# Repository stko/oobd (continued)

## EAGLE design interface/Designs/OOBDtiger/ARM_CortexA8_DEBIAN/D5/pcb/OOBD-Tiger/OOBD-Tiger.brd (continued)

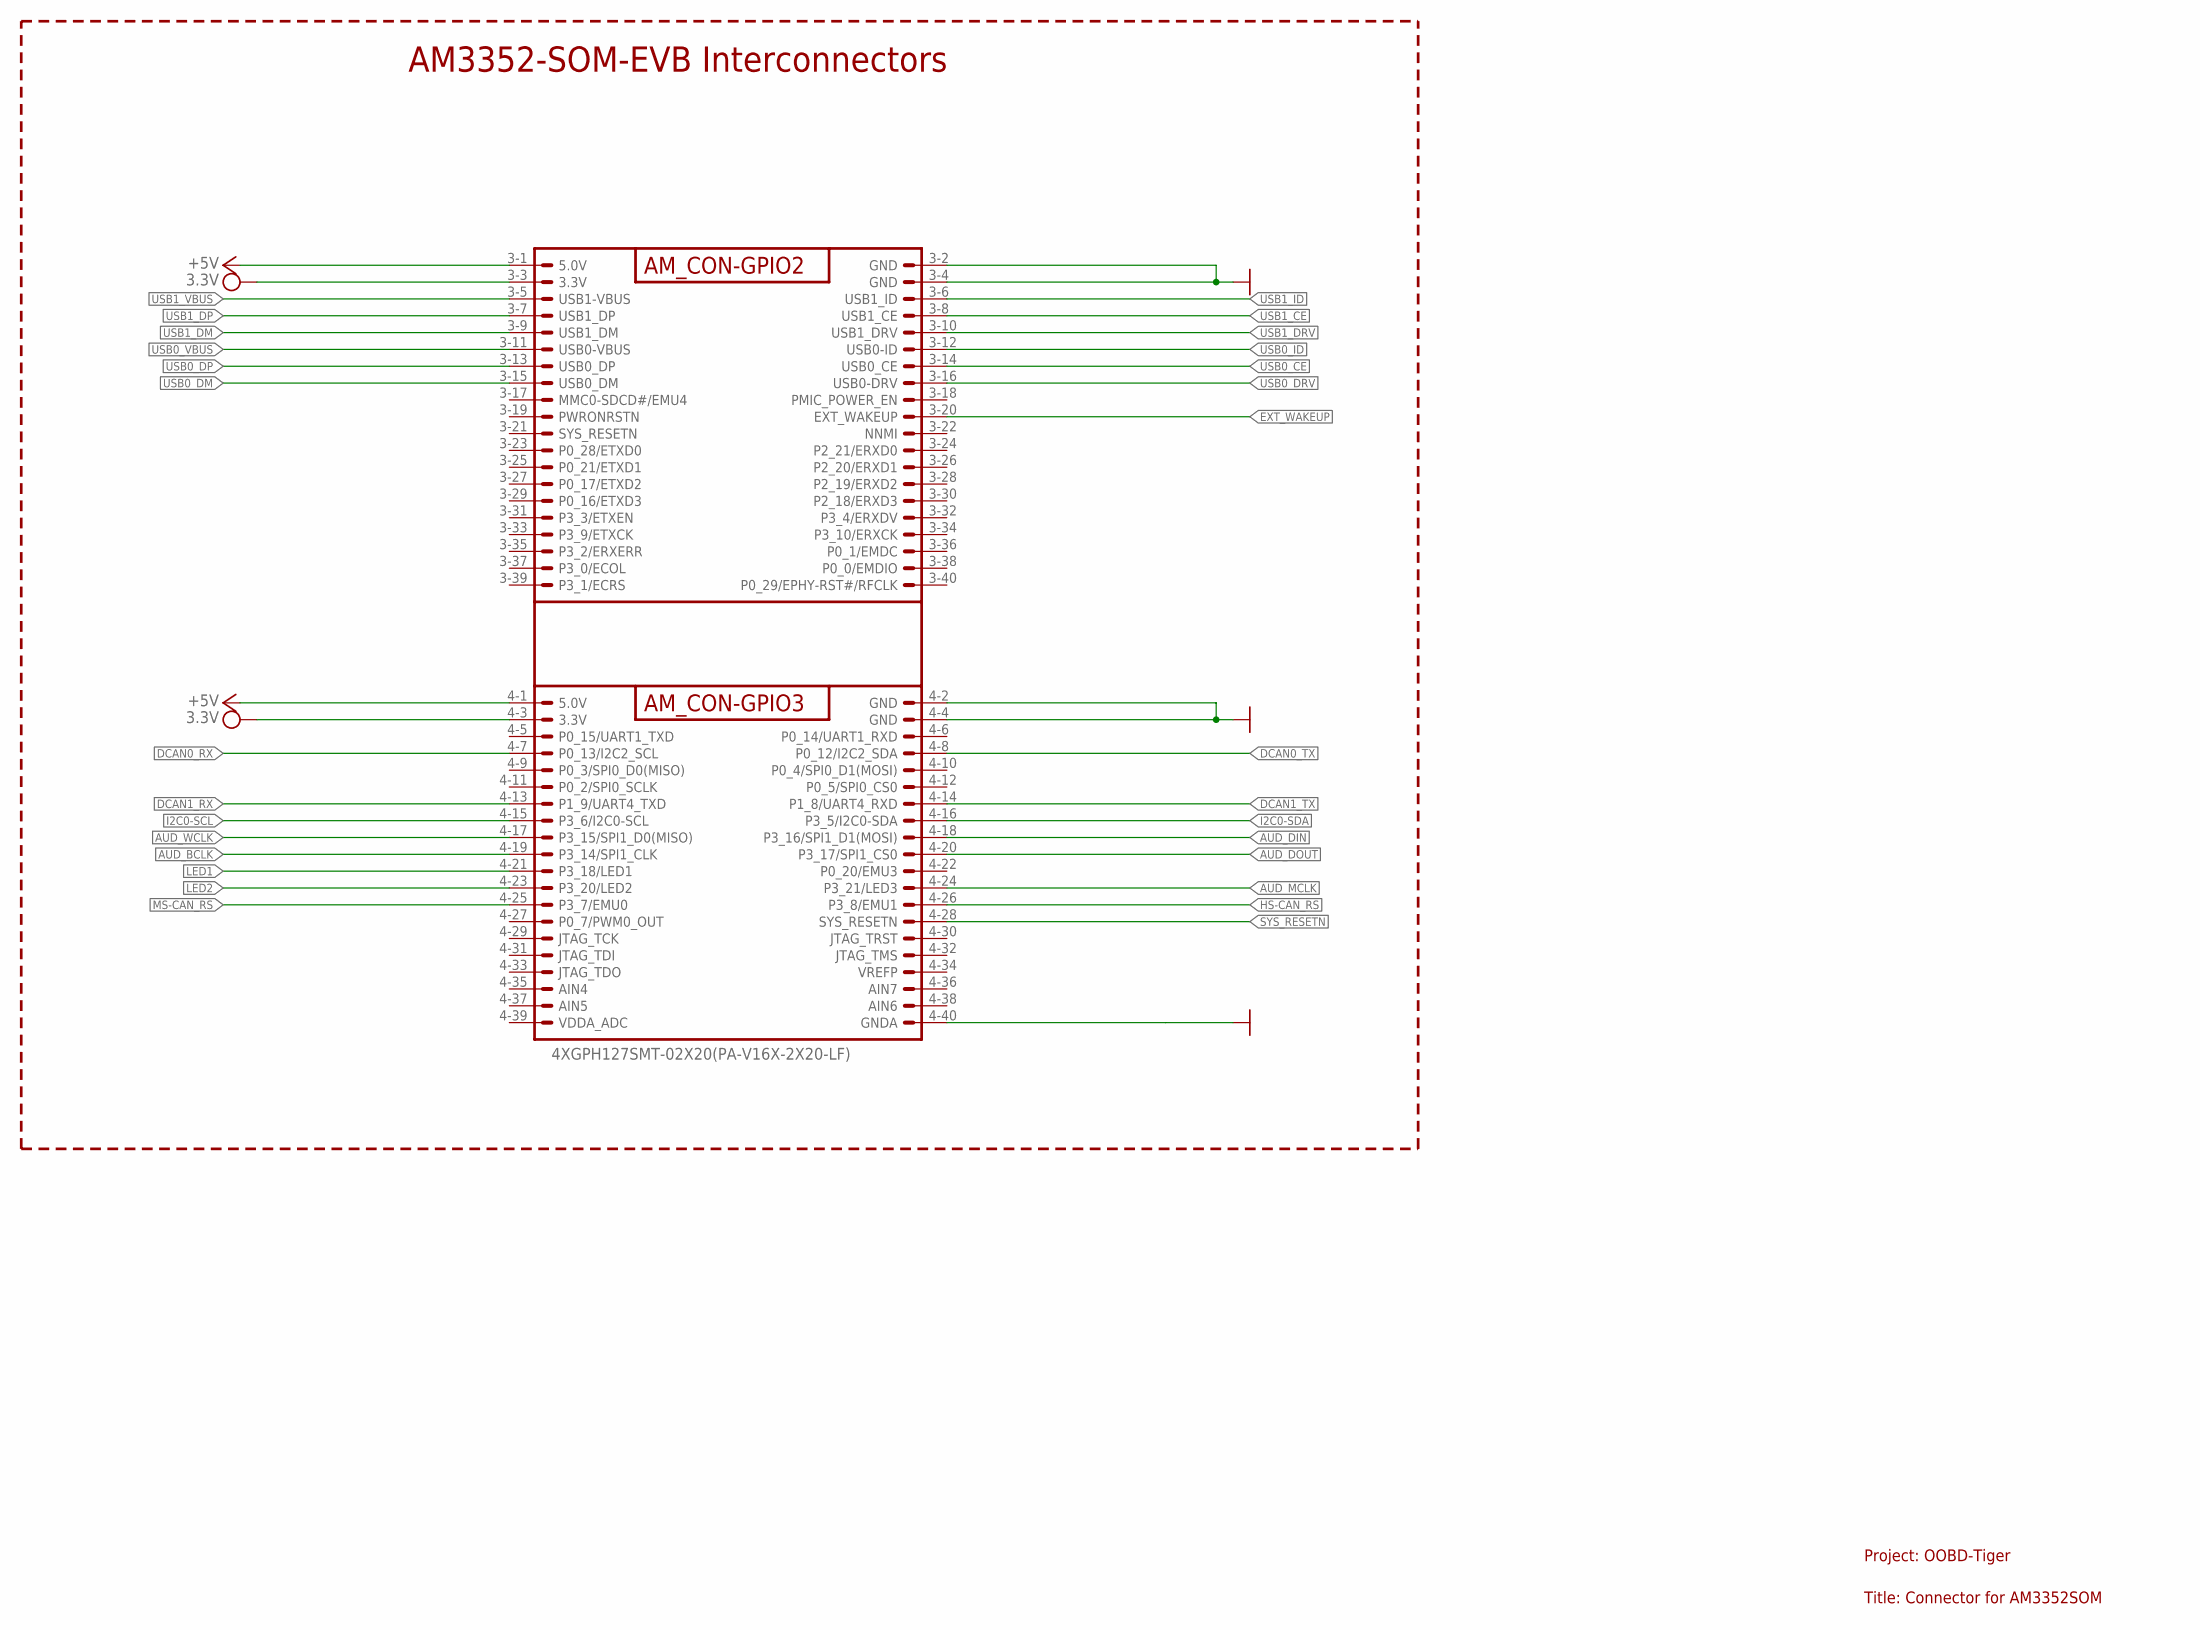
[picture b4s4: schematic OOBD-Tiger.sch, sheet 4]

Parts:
AM3352-SOM-EVB-PLATFORM: 4XGPH127SMT-02X20(PA-V16X-2X20-LF); OOBD-TIGER-AM3352-SOM

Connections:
3V3: AM3352-SOM-EVB-PLATFORM.3-3 (3.3V), AM3352-SOM-EVB-PLATFORM.4-3 (3.3V)
+5V: AM3352-SOM-EVB-PLATFORM.3-1 (5.0V), AM3352-SOM-EVB-PLATFORM.4-1 (5.0V); also elsewhere on the board
AUD_BCLK: AM3352-SOM-EVB-PLATFORM.4-19 (P3_14/SPI1_CLK); also elsewhere on the board
AUD_DIN: AM3352-SOM-EVB-PLATFORM.4-18 (P3_16/SPI1_D1(MOSI)); also elsewhere on the board
AUD_DOUT: AM3352-SOM-EVB-PLATFORM.4-20 (P3_17/SPI1_CS0); also elsewhere on the board
AUD_MCLK: AM3352-SOM-EVB-PLATFORM.4-24 (P3_21/LED3); also elsewhere on the board
AUD_WCLK: AM3352-SOM-EVB-PLATFORM.4-17 (P3_15/SPI1_D0(MISO)); also elsewhere on the board
DCAN0_RX: AM3352-SOM-EVB-PLATFORM.4-7 (P0_13/I2C2_SCL); also elsewhere on the board
DCAN0_TX: AM3352-SOM-EVB-PLATFORM.4-8 (P0_12/I2C2_SDA); also elsewhere on the board
DCAN1_RX: AM3352-SOM-EVB-PLATFORM.4-13 (P1_9/UART4_TXD); also elsewhere on the board
DCAN1_TX: AM3352-SOM-EVB-PLATFORM.4-14 (P1_8/UART4_RXD); also elsewhere on the board
EXT_WAKEUP: AM3352-SOM-EVB-PLATFORM.3-20 (EXT_WAKEUP); also elsewhere on the board
GND: AM3352-SOM-EVB-PLATFORM.3-2 (GND), AM3352-SOM-EVB-PLATFORM.3-4 (GND), AM3352-SOM-EVB-PLATFORM.4-2 (GND), AM3352-SOM-EVB-PLATFORM.4-4 (GND), AM3352-SOM-EVB-PLATFORM.4-40 (GNDA); also elsewhere on the board
HS-CAN_RS: AM3352-SOM-EVB-PLATFORM.4-26 (P3_8/EMU1); also elsewhere on the board
I2C0-SCL: AM3352-SOM-EVB-PLATFORM.4-15 (P3_6/I2C0-SCL); also elsewhere on the board
I2C0-SDA: AM3352-SOM-EVB-PLATFORM.4-16 (P3_5/I2C0-SDA); also elsewhere on the board
LED1: AM3352-SOM-EVB-PLATFORM.4-21 (P3_18/LED1); also elsewhere on the board
LED2: AM3352-SOM-EVB-PLATFORM.4-23 (P3_20/LED2); also elsewhere on the board
MS-CAN_RS: AM3352-SOM-EVB-PLATFORM.4-25 (P3_7/EMU0); also elsewhere on the board
SYS_RESETN: AM3352-SOM-EVB-PLATFORM.4-28 (SYS_RESETN); also elsewhere on the board
USB0_CE: AM3352-SOM-EVB-PLATFORM.3-14 (USB0_CE); also elsewhere on the board
USB0_DM: AM3352-SOM-EVB-PLATFORM.3-15 (USB0_DM); also elsewhere on the board
USB0_DP: AM3352-SOM-EVB-PLATFORM.3-13 (USB0_DP); also elsewhere on the board
USB0_DRV: AM3352-SOM-EVB-PLATFORM.3-16 (USB0-DRV); also elsewhere on the board
USB0_ID: AM3352-SOM-EVB-PLATFORM.3-12 (USB0-ID); also elsewhere on the board
USB0_VBUS: AM3352-SOM-EVB-PLATFORM.3-11 (USB0-VBUS); also elsewhere on the board
USB1_CE: AM3352-SOM-EVB-PLATFORM.3-8 (USB1_CE); also elsewhere on the board
USB1_DM: AM3352-SOM-EVB-PLATFORM.3-9 (USB1_DM); also elsewhere on the board
USB1_DP: AM3352-SOM-EVB-PLATFORM.3-7 (USB1_DP); also elsewhere on the board
USB1_DRV: AM3352-SOM-EVB-PLATFORM.3-10 (USB1_DRV); also elsewhere on the board
USB1_ID: AM3352-SOM-EVB-PLATFORM.3-6 (USB1_ID); also elsewhere on the board
USB1_VBUS: AM3352-SOM-EVB-PLATFORM.3-5 (USB1-VBUS); also elsewhere on the board

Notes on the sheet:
AM3352-SOM-EVB Interconnectors
Project: OOBD-Tiger
Title: Connector for AM3352SOM

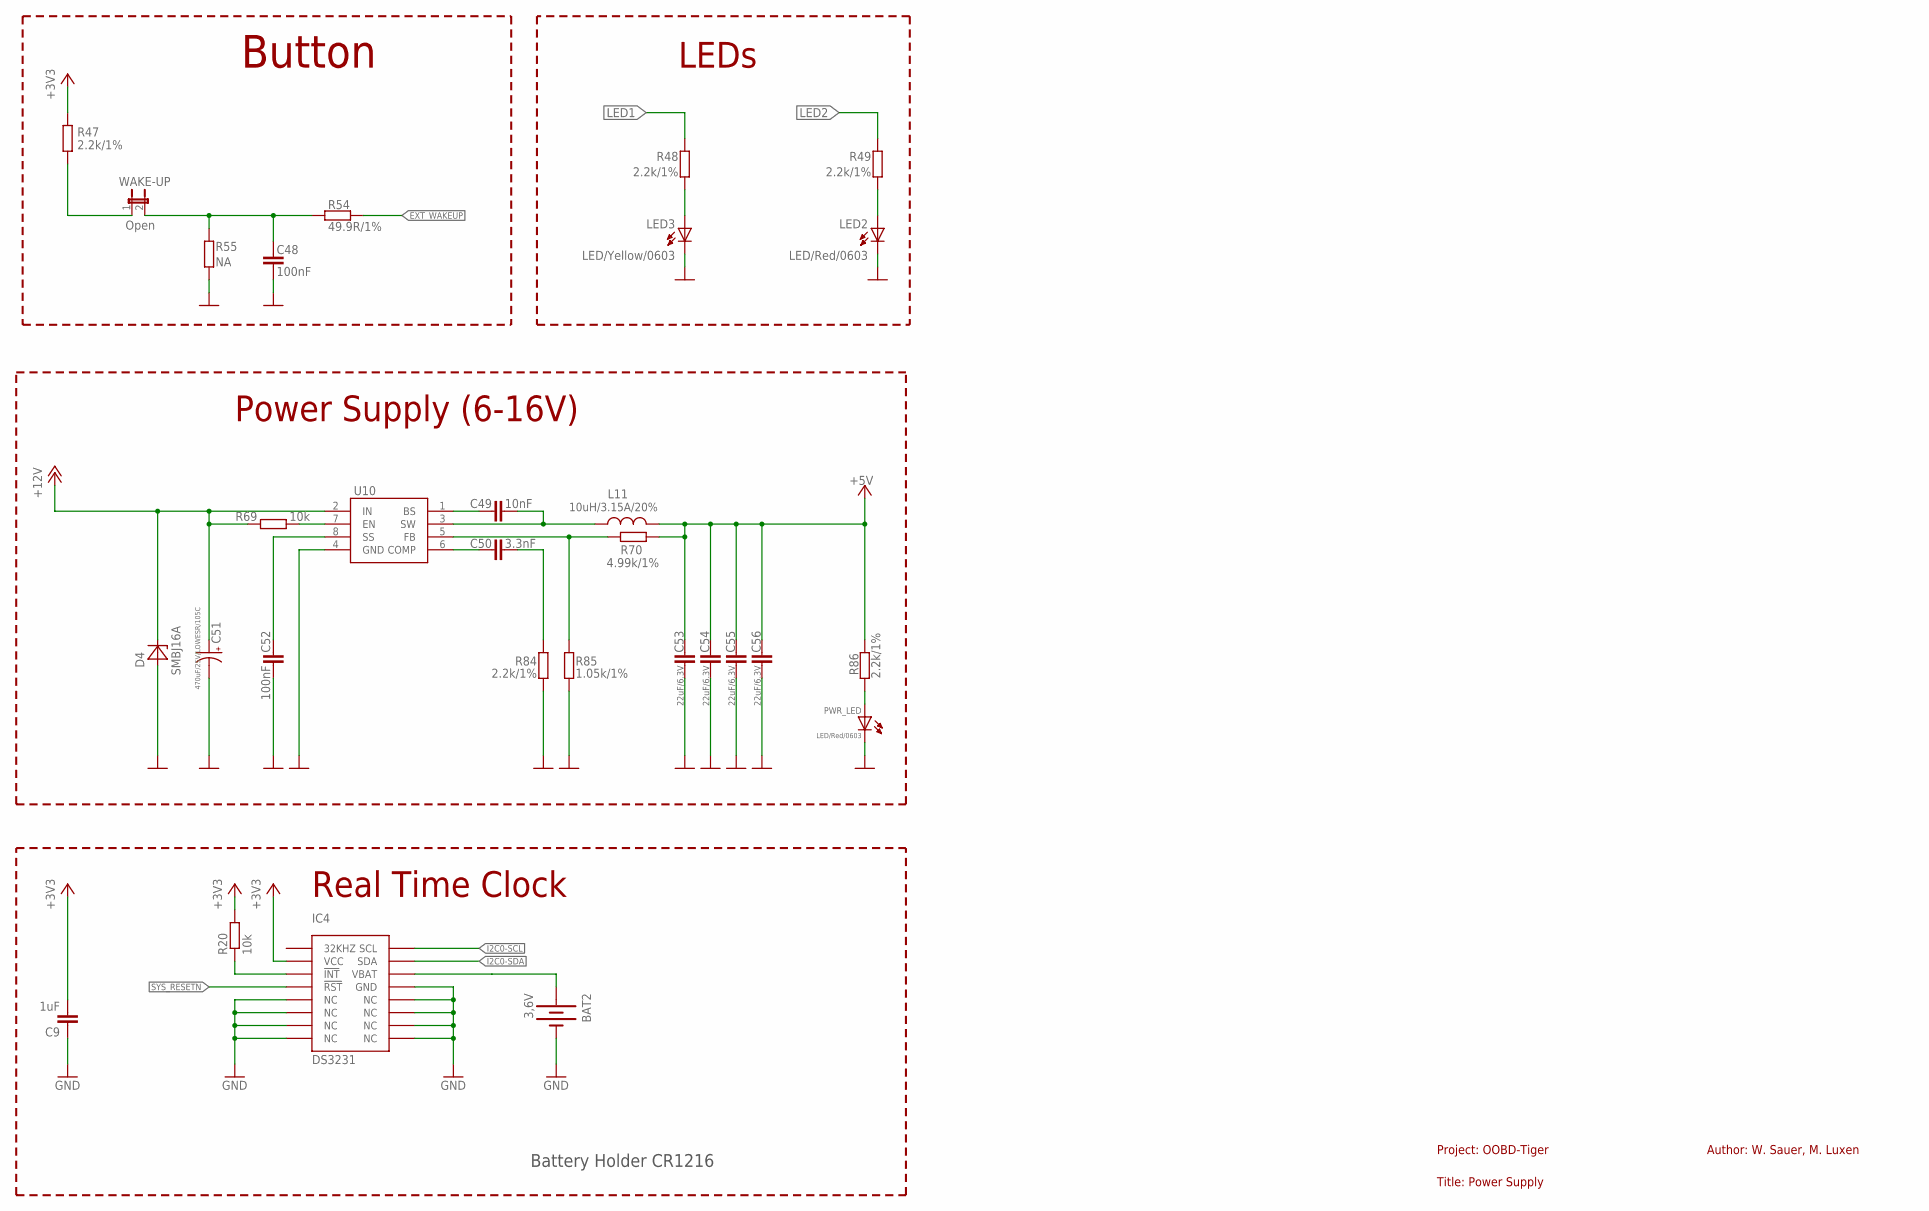
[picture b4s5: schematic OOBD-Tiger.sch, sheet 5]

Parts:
BAT2: 3,6V; BATTCON_12MM_PTH
C9: 1uF; C0603
C48, C52: 100nF; C0603
C49: 10nF; C0603
C50: 3.3nF; C0603
C51: 470uF/25V/LOWESR/105C; PANASONIC_D
C53, C54, C55, C56: 22uF/6.3V; C0603
D4: SMBJ16A; DO214AA
IC4: DS3231; SOIC-16W
L11: 10uH/3.15A/20%; 8X8MM_3131
LED2: LED/Red/0603; LED_0603
LED3: LED/Yellow/0603; LED_0603
PWR_LED: LED/Red/0603; LED-0603
R20, R69: 10k; R0603
R47, R48, R49, R84, R86: 2.2k/1%; R0603
R54: 49.9R/1%; R0603
R55: NA; R0603
R70: 4.99k/1%; R0603
R85: 1.05k/1%; R0603
U10: MP1482DS; SOIC8
WAKE-UP: Open; 1X02_LOCK

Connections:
+3V3: C9.2, IC4.2 (VCC), R20.2, R47.2; also elsewhere on the board
+5V: C53.1, C54.1, C55.1, C56.1, L11.2, R70.2, R86.1; also elsewhere on the board
+12V: C51.+, D4.C, R69.1, U10.2 (IN); also elsewhere on the board
EXT_WAKEUP: R54.1; also elsewhere on the board
GND: BAT2.GND (-), C9.1, C48.2, C51.-, C52.2, C53.2, C54.2, C55.2, C56.2, D4.A, IC4.5 (NC), IC4.6 (NC), IC4.7 (NC), IC4.8 (NC), IC4.9 (NC), IC4.10 (NC), IC4.11 (NC), IC4.12 (NC), IC4.13 (GND), LED2.C, LED3.C, PWR_LED.C, R55.2, R84.2, R85.2, U10.4 (GND); also elsewhere on the board
I2C0-SCL: IC4.16 (SCL); also elsewhere on the board
I2C0-SDA: IC4.15 (SDA); also elsewhere on the board
LED1: R48.1; also elsewhere on the board
LED2: R49.1; also elsewhere on the board
unnamed: LED2.A, R49.2
unnamed: C52.1, U10.8 (SS)
unnamed: R69.2, U10.7 (EN)
unnamed: C49.1, U10.1 (BS)
unnamed: C49.2, L11.1, U10.3 (SW)
unnamed: C50.1, U10.6 (COMP)
unnamed: C50.2, R84.1
unnamed: IC4.3 (!INT), R20.1
unnamed: R47.1, WAKE-UP.1
unnamed: C48.1, R54.2, R55.1, WAKE-UP.2
unnamed: R70.1, R85.1, U10.5 (FB)
unnamed: PWR_LED.A, R86.2
unnamed: LED3.A, R48.2
SYS_RESETN: IC4.4 (!RST); also elsewhere on the board
VBAT: BAT2.VCC@1 (+), IC4.14 (VBAT)

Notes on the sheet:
Button
LEDs
Power Supply (6-16V)
Author: W. Sauer, M. Luxen
Project: OOBD-Tiger
Title: Power Supply
Real Time Clock
Battery Holder CR1216

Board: 2 copper layers, 136 parts (57 on the bottom side), 91 nets, no tracks yet.

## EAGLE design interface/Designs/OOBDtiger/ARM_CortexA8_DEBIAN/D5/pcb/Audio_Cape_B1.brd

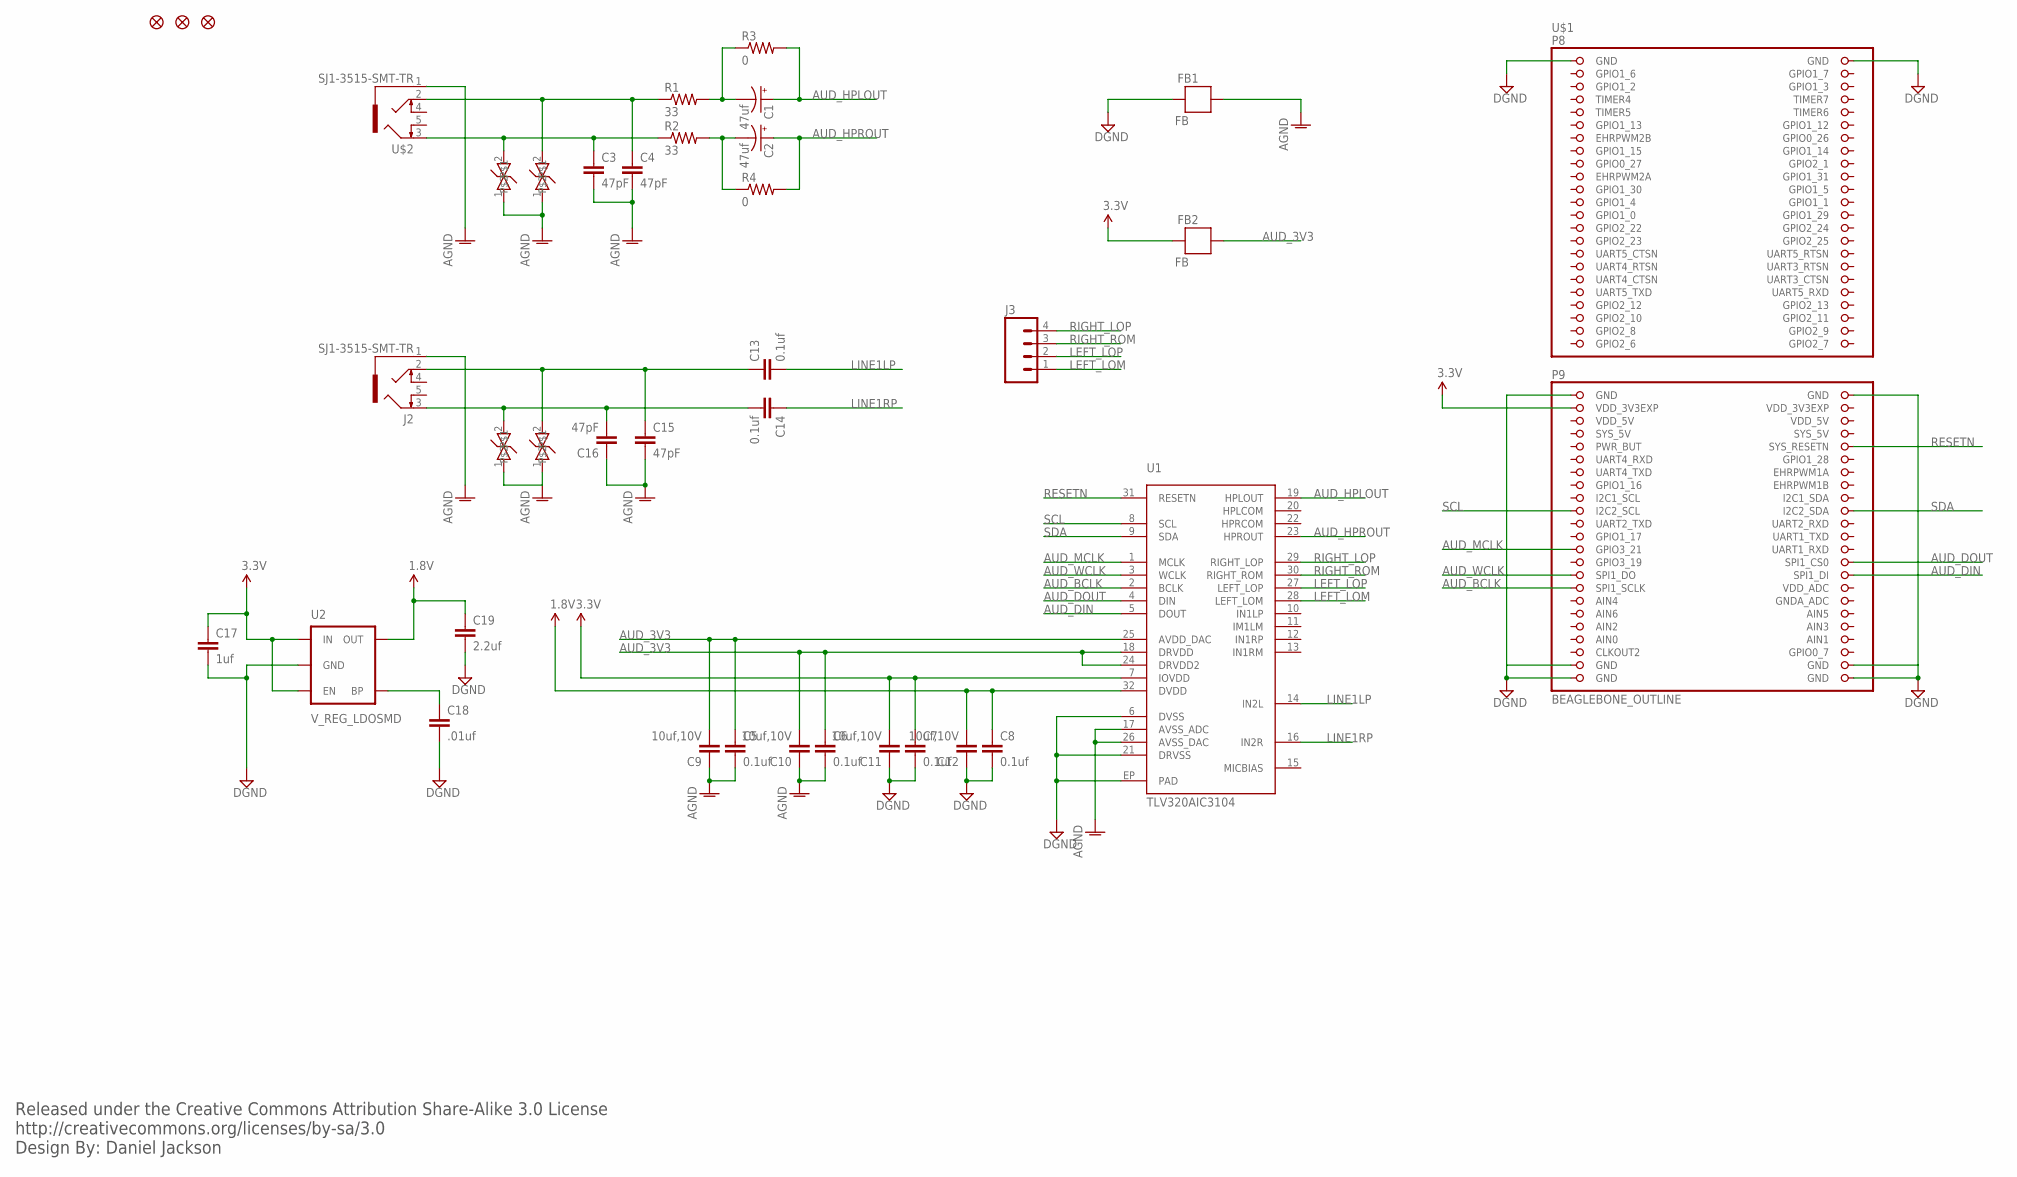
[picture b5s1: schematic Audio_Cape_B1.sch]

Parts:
C1, C2: 47uf; EIA3216
C3, C4, C15, C16: 47pF; 0402-CAP
C5, C6, C7, C8, C13, C14: 0.1uf; 0402-CAP
C9, C10, C11, C12: 10uf,10V; 0603-CAP
C17: 1uf; 0402-CAP
C18: .01uf; 0402-CAP
C19: 2.2uf; 0402-CAP
D1, D2, D3, D4: PGB0010603MR; 0603
FB1, FB2: FB; 0603
FID1, FID2, FID3: FIDUCIAL1X2.5; FIDUCIAL-1X2.5
J2: SJ1-3515-SMT-TR; JACK-SMT
J3: M04PTH; 1X04
R1, R2: 33; 0402-RES
R3, R4: 0; 0805
U1: TLV320AIC3104; QFN-32
U2: V_REG_LDOSMD; SOT23-5
U$1: BEAGLEBONE_OUTLINE; BEAGLEBONE_SHIELD
U$2: SJ1-3515-SMT-TR; JACK-SMT

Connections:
1.8V: C8.1, C12.2, C19.1, U1.32 (DVDD), U2.5 (OUT)
3.3V: C7.1, C11.2, C17.1, FB2.2, U1.7 (IOVDD), U2.1 (IN), U2.3 (EN), U$1.49 (VDD_3V3EXP)
AGND: C3.2, C4.2, C5.2, C6.2, C9.1, C10.1, C15.2, C16.1, D1.1, D2.1, D3.1, D4.1, FB1.1, J2.1, U1.17 (AVSS_ADC), U1.26 (AVSS_DAC), U$2.1
AIN0: U$1.85 (AIN0)
AUD_3V3: C5.1, C6.1, C9.2, C10.2, FB2.1, U1.18 (DRVDD), U1.24 (DRVDD2), U1.25 (AVDD_DAC)
AUD_BCLK: U1.2 (BCLK), U$1.77 (SPI1_SCLK)
AUD_DIN: U1.5 (DOUT), U$1.76 (SPI1_DI)
AUD_DOUT: U1.4 (DIN), U$1.74 (SPI1_CS0)
AUD_HPLOUT: C1.A (+), R3.2, U1.19 (HPLOUT)
AUD_HPROUT: C2.A (+), R4.2, U1.23 (HPROUT)
AUD_MCLK: U1.1 (MCLK), U$1.71 (GPIO3_21)
AUD_WCLK: U1.3 (WCLK), U$1.75 (SPI1_DO)
DGND: C7.2, C8.2, C11.1, C12.1, C17.2, C18.2, C19.2, FB1.2, U1.6 (DVSS), U1.21 (DRVSS), U1.EP (PAD), U2.2 (GND), U$1.1 (GND), U$1.2 (GND), U$1.47 (GND), U$1.48 (GND), U$1.89 (GND), U$1.90 (GND), U$1.91 (GND), U$1.92 (GND)
J1: C4.1, D2.2, R1.1, U$2.2
LEFT_LOM: J3.1, U1.28 (LEFT_LOM)
LEFT_LOP: J3.2, U1.27 (LEFT_LOP)
LINE1LP: C13.2, U1.14 (IN2L)
LINE1RP: C14.1, U1.16 (IN2R)
unnamed: C14.2, C16.2, D3.2, J2.3
unnamed: C1.C (-), R1.2, R3.1
unnamed: C2.C (-), R2.2, R4.1
unnamed: C3.1, D1.2, R2.1, U$2.3
unnamed: C13.1, C15.1, D4.2, J2.2
unnamed: C18.1, U2.4 (BP)
RESETN: U1.31 (RESETN), U$1.56 (SYS_RESETN)
RIGHT_LOP: J3.4, U1.29 (RIGHT_LOP)
RIGHT_ROM: J3.3, U1.30 (RIGHT_ROM)
SCL: U1.8 (SCL), U$1.65 (I2C2_SCL)
SDA: U1.9 (SDA), U$1.66 (I2C2_SDA)
SYS_5V: U$1.53 (SYS_5V)
VDD_3V3EXP: U$1.50 (VDD_3V3EXP)
VDD_5V: U$1.51 (VDD_5V), U$1.52 (VDD_5V)

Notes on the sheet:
Released under the Creative Commons Attribution Share-Alike 3.0 License http://creativecommons.org/licenses/by-sa/3.0 Design By: Daniel Jackson

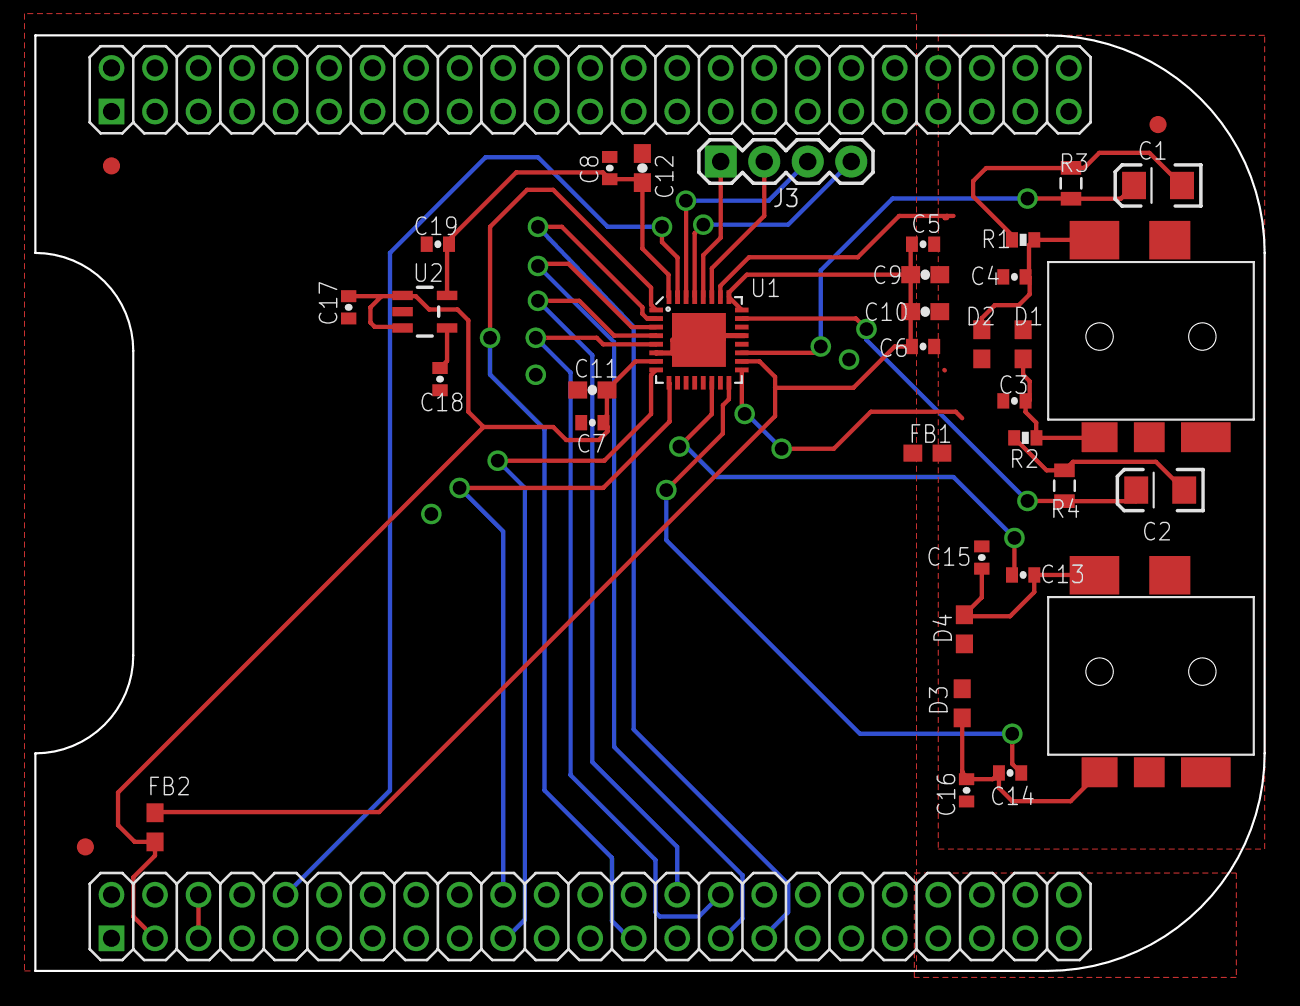
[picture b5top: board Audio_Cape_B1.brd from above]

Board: 2 copper layers, 71.8 x 54.6 mm, 40 parts (0 on the bottom side), 29 nets.

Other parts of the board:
DRILEGEND: DRILEGEND
U$4: CIRCUITCO-LOGO

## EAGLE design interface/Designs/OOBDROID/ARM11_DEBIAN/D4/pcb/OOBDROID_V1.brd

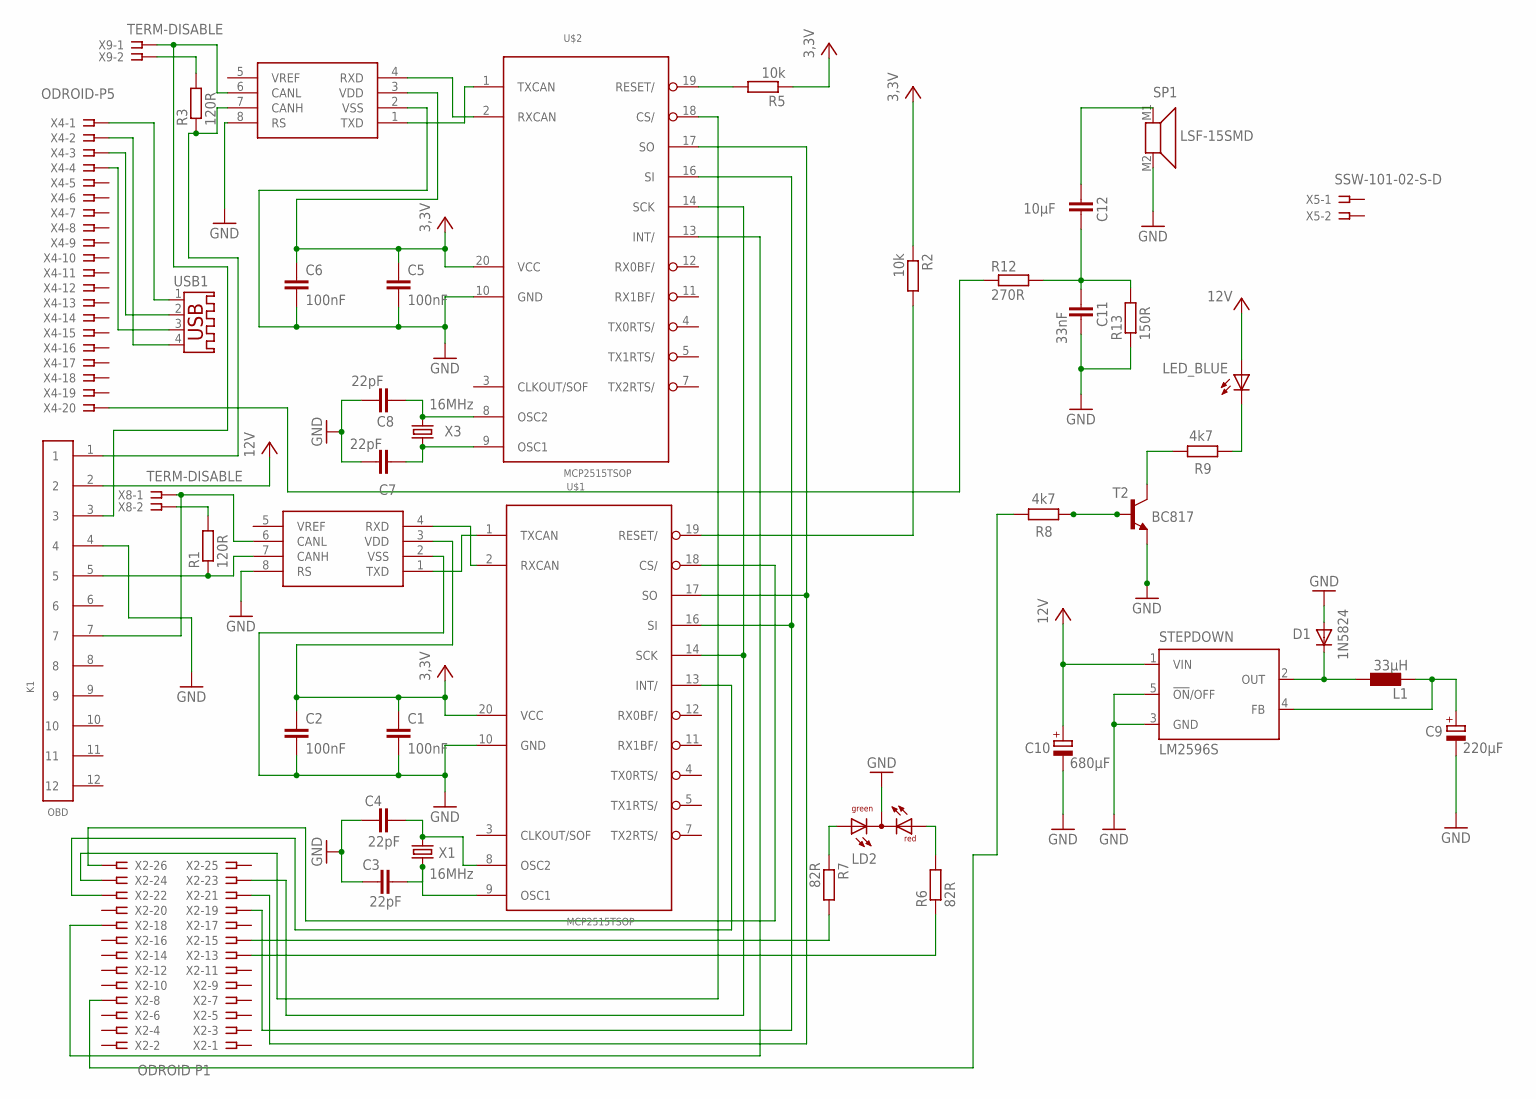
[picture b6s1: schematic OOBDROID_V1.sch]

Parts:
C1, C2, C5, C6: 100nF; C0805
C3, C4, C7, C8: 22pF; C0805
C9: 220µF; E1,8-4
C10: 680µF; E1,8-4
C11: 33nF; C0805
C12: 10µF; C0805
D1: 1N5824; DO214AA
K1: OBD; 653112124022
L1: 33µH; L4532P
LD2: DUOLED-RG-C; DUOLED-C-5MM
LED_BLUE: LED5MM
R1, R3: 120R; R0603
R2, R5: 10k; R0603
R6, R7: 82R; R0603
R8, R9: 4k7; R0603
R12: 270R; R0603
R13: 150R; R0603
SP1: LSF-15SMD; SMS-1308MS-2-R
STEPDOWN: LM2596S; TO263-5
T2: BC817; SOT23
U1, U2: MCP2551; SO08
U$1, U$2: MCP2515TSOP; TSSOP20
USB1: USB-A003
X1, X3: 16MHz; HC49
X2: ODROID P1; SSW-113-02-S-D
X4: ODROID-P5; SSW-120-02-S-S
X5: SSW-101-02-S-D
X8: TERM-DISABLE; SSW-101-02-S-D; MPN CAN-DISABLE
X9: TERM-DISABLE; SSW-101-02-S-D

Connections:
GND: C1.2, C2.2, C3.1, C4.1, C5.2, C6.2, C7.1, C8.1, C9.-, C10.-, C11.1, D1.A, K1.4, LD2.C, R13.1, SP1.M2 (2), STEPDOWN.3 (GND), STEPDOWN.5 (!ON!/OFF), T2.2 (E), U1.2 (VSS), U1.8 (RS), U2.2 (VSS), U2.8 (RS), U$1.10 (GND), U$2.10 (GND)
unnamed: K1.5, R1.1, U1.7 (CANH)
unnamed: D1.C, L1.1, STEPDOWN.2 (OUT)
unnamed: C8.2, U$2.8 (OSC2), X3.2
unnamed: C9.+, L1.2, STEPDOWN.4 (FB)
unnamed: C7.2, U$2.9 (OSC1), X3.1
unnamed: R5.2, U$2.19 (RESET/)
unnamed: U2.4 (RXD), U$2.2 (RXCAN)
unnamed: U2.1 (TXD), U$2.1 (TXCAN)
unnamed: K1.3, U2.6 (CANL), X9.1
unnamed: K1.1, R3.1, U2.7 (CANH)
unnamed: C4.2, U$1.8 (OSC2), X1.2
unnamed: C3.2, U$1.9 (OSC1), X1.1
unnamed: R2.2, U$1.19 (RESET/)
unnamed: U1.4 (RXD), U$1.2 (RXCAN)
unnamed: U1.1 (TXD), U$1.1 (TXCAN)
unnamed: K1.7, U1.6 (CANL), X8.1
unnamed: C12.2, SP1.M1 (1)
unnamed: LED_BLUE.K (C), R9.1
unnamed: U$1.18 (CS/), X2.26
unnamed: R3.2, X9.2
unnamed: LD2.AR, R6.2
unnamed: LD2.AX (AG), R7.1
unnamed: R7.2, X2.15
unnamed: R6.1, X2.13
unnamed: USB1.1, X4.1
unnamed: USB1.4, X4.2
unnamed: USB1.2, X4.3
unnamed: USB1.3, X4.4
unnamed: R12.1, X4.20
unnamed: U$1.13 (INT/), X2.22
unnamed: U$2.13 (INT/), X2.18
unnamed: U$2.18 (CS/), X2.24
unnamed: R9.2, T2.3 (C)
unnamed: R8.1, T2.1 (B)
unnamed: R8.2, X2.8
unnamed: C11.2, C12.1, R12.2, R13.2
unnamed: U$1.16 (SI), U$2.16 (SI), X2.19
unnamed: R1.2, X8.2
unnamed: U$1.17 (SO), U$2.17 (SO), X2.21
unnamed: U$1.14 (SCK), U$2.14 (SCK), X2.23
VCC: C1.1, C2.1, C5.1, C6.1, C10.+, K1.2, LED_BLUE.A, R2.1, R5.1, STEPDOWN.1 (VIN), U1.3 (VDD), U2.3 (VDD), U$1.20 (VCC), U$2.20 (VCC)

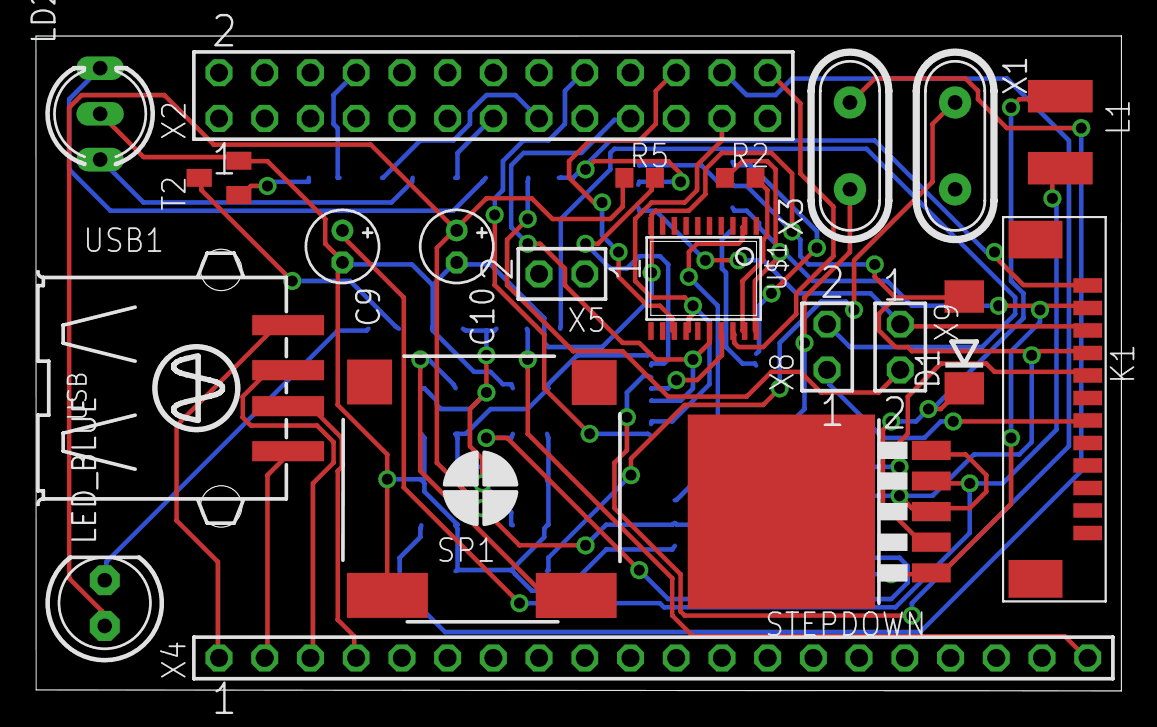
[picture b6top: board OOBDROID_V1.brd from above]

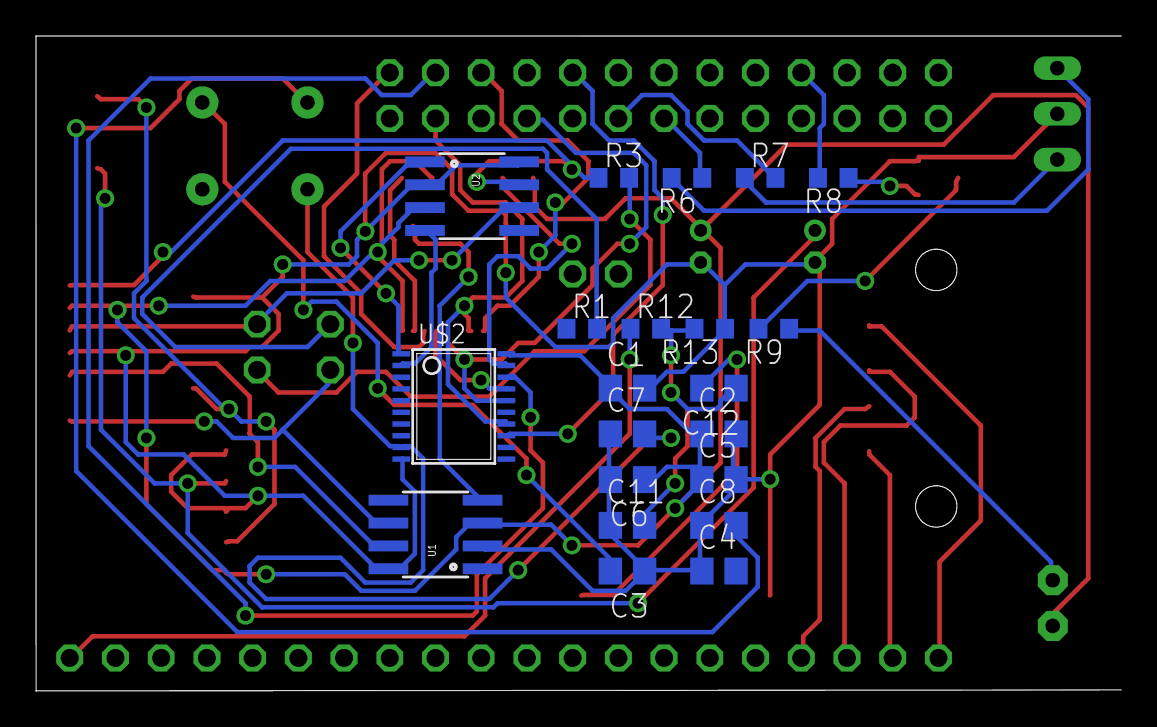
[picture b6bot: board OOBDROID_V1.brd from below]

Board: 2 copper layers, 60.3 x 36.4 mm, 42 parts (21 on the bottom side), 42 nets.

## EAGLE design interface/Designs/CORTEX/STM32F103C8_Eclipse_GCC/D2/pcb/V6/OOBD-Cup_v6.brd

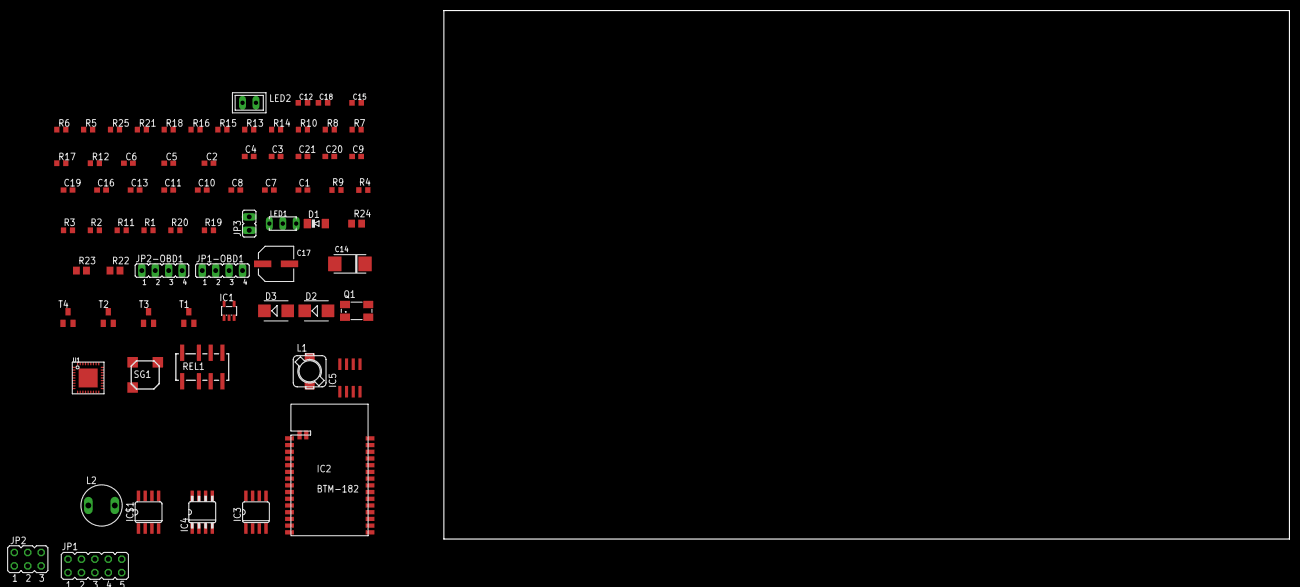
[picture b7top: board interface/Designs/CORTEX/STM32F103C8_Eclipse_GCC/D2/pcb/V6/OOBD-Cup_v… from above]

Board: 2 copper layers, 160.0 x 100.0 mm, 72 parts (0 on the bottom side), 54 nets, no tracks yet.

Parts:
C1, C2, C5, C6, C7, C8, C10, C11, C13, C16, C19: 100nF; C0603
C3, C4: 15p; C0603
C9: 10nF; C0603
C12: 1µF; C0603K
C14: 220µF; C6032-TE-C
C15: 220pF; C0603K
C17: 47µ/35V; SV-D
C18: 100nF; C0603K
C20, C21: 100n; C0603
D1: 1N4148; MINIMELF
D2, D3: B140; SMB
IC1: 24LC16; SOT23-5L
IC2: BTM-182
IC3: PCA82C250T; SO08
IC4: MC34063-SO; SO8
IC5: 78L05SMD; SO08
IC$1: SI9243AEY; SO08
JP1: Program; JP5Q
JP1-OBD1, JP2-OBD1: JP4
JP2: ext. WLAN; JP3Q
JP3: JP1
L1: 47uH; PIS2408
L2: 47µH; 07HCP-XXXX-50
LED1: Rt/Gr; DUOLED2X5
LED2: Blue; U57X32
Q1: 8MHz; CTS406
R1: 130k; R0603
R2: 27k; R0603
R3, R4, R5, R6: 10k; R0603
R7, R8: 82R; R0603
R9, R10, R11, R13, R14, R15, R16: 4k7; R0603
R12, R20: 510R; R0603
R17: 180k; R0603
R18: 47k; R0603
R19: 120R; R0603
R21: 3k3; R0603
R22, R23, R24: 1R; R0805
R25: 5k6; R0603
REL1: FTR-B4GA
SG1: MBWOE; BME0603SA
T1, T2, T3, T4: BC817; SOT23
U1: STM32F10XTXU6; VFQFPN36

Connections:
3V3_BTM182: C5.1, C6.1, IC2.P$14, IC2.P$16, JP1.9
+3V3: C2.1, C10.1, C11.1, C12.1, C13.1, C14.+, C16.1, IC1.4, JP1.8, JP1.10, L1.P$1, L2.1, R3.2, R9.2, R11.2, R25.2, SG1.(+)LEAD, U1.1, U1.6, U1.19, U1.27
+5V: C7.1, C19.1, C21.1, IC3.3, IC5.1, IC$1.3
+12V: C17.+, C18.1, C20.1, D1.C, D3.C, IC4.6, IC5.8, JP2.2, LED2.A, R1.2, R22.2, R23.2, R24.2, REL1.1
BOOT0: JP1.7, R4.2, U1.35
BTM_RX: IC2.P$10, JP1.1
BTM_TX: IC2.P$9, JP1.3
BT_RES-: IC2.P$21, U1.29
BUZZER: R13.1, U1.13
CAN-RXD: IC3.4, U1.23
CAN-TXD: IC3.1, U1.24
CAN_SW: R16.1, U1.30
GND: C1.2, C2.2, C3.1, C4.1, C5.2, C6.2, C7.2, C8.2, C9.2, C10.2, C11.2, C12.2, C13.2, C14.-, C15.2, C16.2, C17.-, C18.2, C19.2, C20.2, C21.2, D2.A, IC1.2, IC2.P$15, IC3.2, IC3.8, IC4.4, IC5.2, IC5.3, IC5.6, IC5.7, IC$1.5, JP1.6, JP2.5, JP2-OBD1.3, LED1.K, R2.1, R4.1, R5.2, R6.2, R18.1, R21.2, T1.2, T2.2, T3.2, T4.2, U1.5, U1.17, U1.18, U1.26, U1.36
HS_CAN-H: JP1-OBD1.1, REL1.2
HS_CAN-L: JP1-OBD1.2, REL1.7
K-LINE: C9.1, IC$1.6, JP2-OBD1.2, R20.1
L-LINE: JP2-OBD1.1, R12.1, T1.3
LED1: R8.1, U1.32
LED1_GR: JP2.1, LED1.AG, R7.2
LED1_RT: JP2.3, LED1.AR, R8.2
LED2: R7.1, U1.31
LED2_BL: JP2.4, LED2.K, R15.1
LED_BLUE: R14.1, U1.14
MODE1: R6.1, U1.25
MS_CAN-H: JP1-OBD1.3, REL1.4
MS_CAN-L: JP1-OBD1.4, REL1.5
unnamed: C4.2, Q1.1, U1.2
unnamed: C3.2, Q1.3, U1.3
unnamed: IC3.6, JP3.1, REL1.6
unnamed: IC3.7, R19.2, REL1.3
unnamed: R10.1, U1.11
unnamed: R14.2, T3.1
unnamed: R15.2, T3.3
unnamed: C15.1, IC4.3
unnamed: IC4.1, IC4.7, IC4.8, R22.1, R23.1, R24.1
unnamed: IC4.5, R21.1, R25.1
unnamed: D2.C, IC4.2, L1.P$2, L2.2
unnamed: C1.1, R1.1, R2.2, U1.15
unnamed: JP3.2, R19.1
unnamed: R10.2, T1.1
unnamed: R5.1, U1.28
unnamed: IC1.1, R9.1, U1.33
unnamed: R16.2, T4.1
unnamed: IC1.3, R11.1, U1.34
unnamed: SG1.(-)LEAD, T2.3
unnamed: R13.2, T2.1
unnamed: D1.A, R17.2, REL1.8, T4.3
REL_DIAG: R17.1, R18.2, U1.16
RESET-: JP1.5, R3.1, U1.4
RX_K: IC$1.1, U1.10
STM_RXD: JP1.4, U1.22
STM_TXD: JP1.2, U1.21
TX: IC$1.4, U1.9
VBAT: C8.1, D3.A, IC$1.7, JP2.6, JP2-OBD1.4, R12.2, R20.2
